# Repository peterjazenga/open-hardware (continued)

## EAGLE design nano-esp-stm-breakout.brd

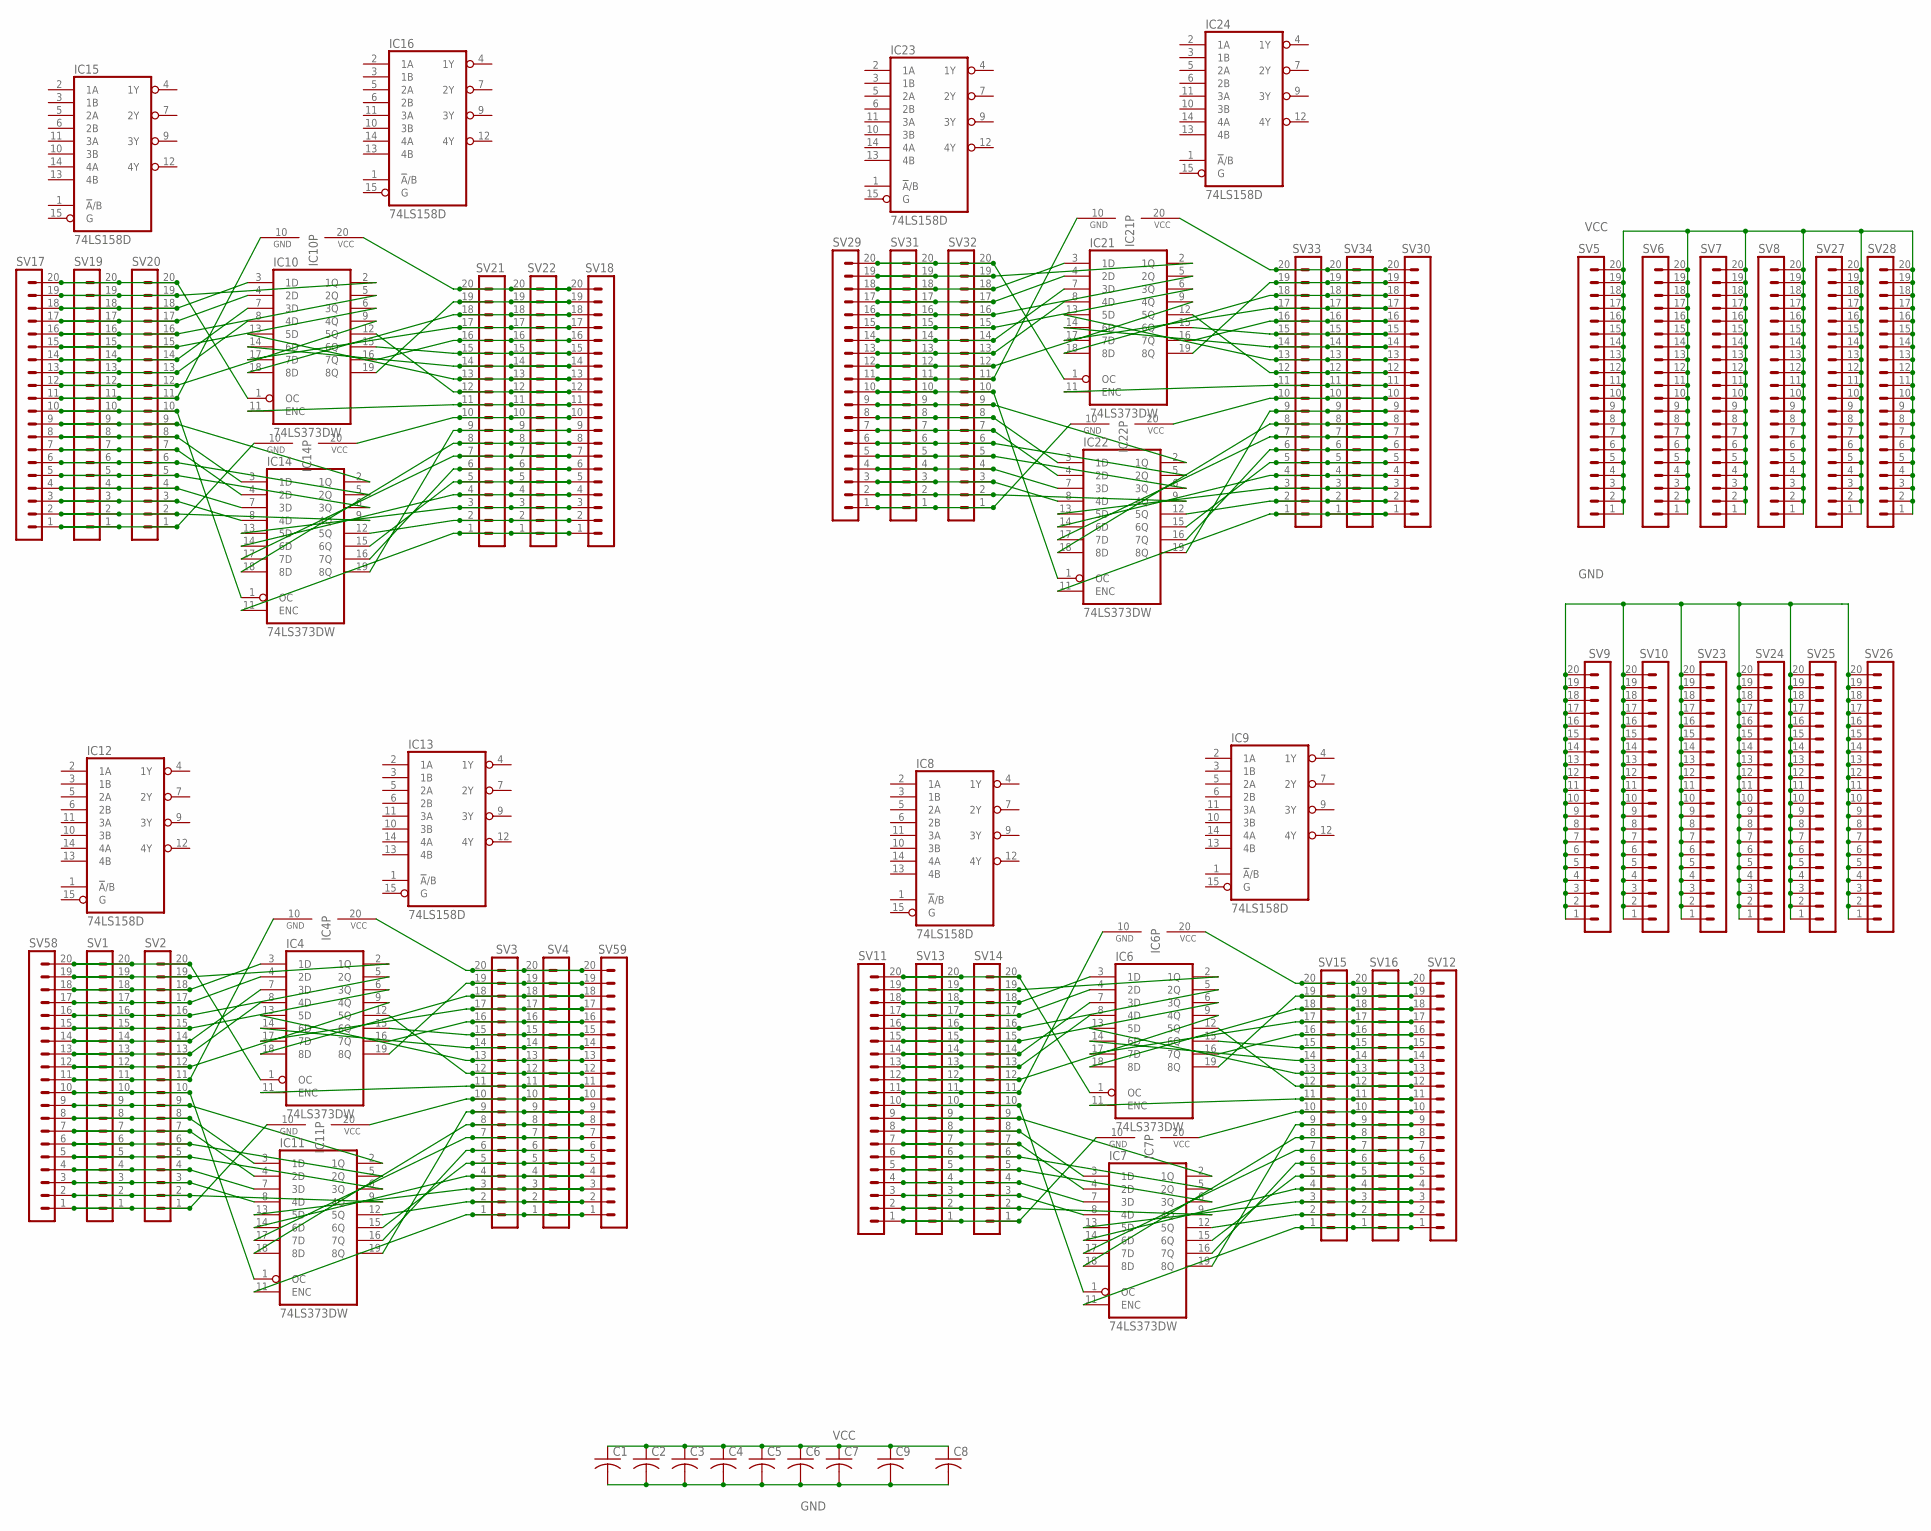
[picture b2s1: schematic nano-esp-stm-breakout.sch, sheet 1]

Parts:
C1, C2, C3, C4, C5, C6, C7, C8, C9: C-USC0805; C0805
IC4, IC6, IC7, IC10, IC11, IC14, IC21, IC22: 74LS373DW; SO20W
IC8, IC9, IC12, IC13, IC15, IC16, IC23, IC24: 74LS158D; SO16
SV1, SV2, SV3, SV4, SV5, SV6, SV7, SV8, SV9, SV10, SV11, SV12, SV13, SV14, SV15, SV16, SV17, SV18, SV19, SV20, SV21, SV22, SV23, SV24, SV25, SV26, SV27, SV28, SV29, SV30, SV31, SV32, SV33, SV34, SV58, SV59: MA20-1

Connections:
GND: C1.2, C2.2, C3.2, C4.2, C5.2, C6.2, C7.2, C8.2, C9.2, IC8.8 (GND), IC9.8 (GND), IC12.8 (GND), IC13.8 (GND), IC15.8 (GND), IC16.8 (GND), IC23.8 (GND), IC24.8 (GND), SV9.1, SV9.2, SV9.3, SV9.4, SV9.5, SV9.6, SV9.7, SV9.8, SV9.9, SV9.10, SV9.11, SV9.12, SV9.13, SV9.14, SV9.15, SV9.16, SV9.17, SV9.18, SV9.19, SV9.20, SV10.1, SV10.2, SV10.3, SV10.4, SV10.5, SV10.6, SV10.7, SV10.8, SV10.9, SV10.10, SV10.11, SV10.12, SV10.13, SV10.14, SV10.15, SV10.16, SV10.17, SV10.18, SV10.19, SV10.20, SV23.1, SV23.2, SV23.3, SV23.4, SV23.5, SV23.6, SV23.7, SV23.8, SV23.9, SV23.10, SV23.11, SV23.12, SV23.13, SV23.14, SV23.15, SV23.16, SV23.17, SV23.18, SV23.19, SV23.20, SV24.1, SV24.2, SV24.3, SV24.4, SV24.5, SV24.6, SV24.7, SV24.8, SV24.9, SV24.10, SV24.11, SV24.12, SV24.13, SV24.14, SV24.15, SV24.16, SV24.17, SV24.18, SV24.19, SV24.20, SV25.1, SV25.2, SV25.3, SV25.4, SV25.5, SV25.6, SV25.7, SV25.8, SV25.9, SV25.10, SV25.11, SV25.12, SV25.13, SV25.14, SV25.15, SV25.16, SV25.17, SV25.18, SV25.19, SV25.20, SV26.1, SV26.2, SV26.3, SV26.4, SV26.5, SV26.6, SV26.7, SV26.8, SV26.9, SV26.10, SV26.11, SV26.12, SV26.13, SV26.14, SV26.15, SV26.16, SV26.17, SV26.18, SV26.19, SV26.20; also elsewhere on the board
unnamed: IC7.9 (4Q), SV11.2, SV13.2, SV14.2
unnamed: IC7.7 (3D), SV11.4, SV13.4, SV14.4
unnamed: IC7.6 (3Q), SV11.5, SV13.5, SV14.5
unnamed: IC7.5 (2Q), SV11.6, SV13.6, SV14.6
unnamed: IC7.3 (1D), SV11.8, SV13.8, SV14.8
unnamed: IC7.2 (1Q), SV11.9, SV13.9, SV14.9
unnamed: IC7.1 (OC), SV11.10, SV13.10, SV14.10
unnamed: IC6.10 (GND), SV11.11, SV13.11, SV14.11
unnamed: IC6.9 (4Q), SV11.12, SV13.12, SV14.12
unnamed: IC6.7 (3D), SV11.14, SV13.14, SV14.14
unnamed: IC6.6 (3Q), SV11.15, SV13.15, SV14.15
unnamed: IC6.5 (2Q), SV11.16, SV13.16, SV14.16
unnamed: IC6.3 (1D), SV11.18, SV13.18, SV14.18
unnamed: IC6.2 (1Q), SV11.19, SV13.19, SV14.19
unnamed: IC6.1 (OC), SV11.20, SV13.20, SV14.20
unnamed: IC7.11 (ENC), SV12.1, SV15.1, SV16.1
unnamed: IC7.12 (5Q), SV12.2, SV15.2, SV16.2
unnamed: IC7.13 (5D), SV12.3, SV15.3, SV16.3
unnamed: IC7.14 (6D), SV12.4, SV15.4, SV16.4
unnamed: IC7.15 (6Q), SV12.5, SV15.5, SV16.5
unnamed: IC7.16 (7Q), SV12.6, SV15.6, SV16.6
unnamed: IC7.17 (7D), SV12.7, SV15.7, SV16.7
unnamed: IC7.18 (8D), SV12.8, SV15.8, SV16.8
unnamed: IC7.19 (8Q), SV12.9, SV15.9, SV16.9
unnamed: IC7.20 (VCC), SV12.10, SV15.10, SV16.10
unnamed: IC6.11 (ENC), SV12.11, SV15.11, SV16.11
unnamed: IC6.12 (5Q), SV12.12, SV15.12, SV16.12
unnamed: IC6.13 (5D), SV12.13, SV15.13, SV16.13
unnamed: IC6.14 (6D), SV12.14, SV15.14, SV16.14
unnamed: IC6.15 (6Q), SV12.15, SV15.15, SV16.15
unnamed: IC6.16 (7Q), SV12.16, SV15.16, SV16.16
unnamed: IC6.17 (7D), SV12.17, SV15.17, SV16.17
unnamed: IC6.18 (8D), SV12.18, SV15.18, SV16.18
unnamed: IC6.19 (8Q), SV12.19, SV15.19, SV16.19
unnamed: IC7.10 (GND), SV11.1, SV13.1, SV14.1
unnamed: IC7.8 (4D), SV11.3, SV13.3, SV14.3
unnamed: IC7.4 (2D), SV11.7, SV13.7, SV14.7
unnamed: IC6.8 (4D), SV11.13, SV13.13, SV14.13
unnamed: IC6.4 (2D), SV11.17, SV13.17, SV14.17
unnamed: IC6.20 (VCC), SV12.20, SV15.20, SV16.20
unnamed: IC14.9 (4Q), SV17.2, SV19.2, SV20.2
unnamed: IC14.7 (3D), SV17.4, SV19.4, SV20.4
unnamed: IC14.6 (3Q), SV17.5, SV19.5, SV20.5
unnamed: IC14.5 (2Q), SV17.6, SV19.6, SV20.6
unnamed: IC14.3 (1D), SV17.8, SV19.8, SV20.8
unnamed: IC14.2 (1Q), SV17.9, SV19.9, SV20.9
unnamed: IC14.1 (OC), SV17.10, SV19.10, SV20.10
unnamed: IC10.10 (GND), SV17.11, SV19.11, SV20.11
unnamed: IC10.9 (4Q), SV17.12, SV19.12, SV20.12
unnamed: IC10.7 (3D), SV17.14, SV19.14, SV20.14
unnamed: IC10.6 (3Q), SV17.15, SV19.15, SV20.15
unnamed: IC10.5 (2Q), SV17.16, SV19.16, SV20.16
unnamed: IC10.3 (1D), SV17.18, SV19.18, SV20.18
unnamed: IC10.2 (1Q), SV17.19, SV19.19, SV20.19
unnamed: IC10.1 (OC), SV17.20, SV19.20, SV20.20
unnamed: IC14.11 (ENC), SV18.1, SV21.1, SV22.1
unnamed: IC14.12 (5Q), SV18.2, SV21.2, SV22.2
unnamed: IC14.13 (5D), SV18.3, SV21.3, SV22.3
unnamed: IC14.14 (6D), SV18.4, SV21.4, SV22.4
unnamed: IC14.15 (6Q), SV18.5, SV21.5, SV22.5
unnamed: IC14.16 (7Q), SV18.6, SV21.6, SV22.6
unnamed: IC14.17 (7D), SV18.7, SV21.7, SV22.7
unnamed: IC14.18 (8D), SV18.8, SV21.8, SV22.8
unnamed: IC14.19 (8Q), SV18.9, SV21.9, SV22.9
unnamed: IC14.20 (VCC), SV18.10, SV21.10, SV22.10
unnamed: IC10.11 (ENC), SV18.11, SV21.11, SV22.11
unnamed: IC10.12 (5Q), SV18.12, SV21.12, SV22.12
unnamed: IC10.13 (5D), SV18.13, SV21.13, SV22.13
unnamed: IC10.14 (6D), SV18.14, SV21.14, SV22.14
unnamed: IC10.15 (6Q), SV18.15, SV21.15, SV22.15
unnamed: IC10.16 (7Q), SV18.16, SV21.16, SV22.16
unnamed: IC10.17 (7D), SV18.17, SV21.17, SV22.17
unnamed: IC10.18 (8D), SV18.18, SV21.18, SV22.18
unnamed: IC10.19 (8Q), SV18.19, SV21.19, SV22.19
unnamed: IC14.10 (GND), SV17.1, SV19.1, SV20.1
unnamed: IC14.8 (4D), SV17.3, SV19.3, SV20.3
unnamed: IC14.4 (2D), SV17.7, SV19.7, SV20.7
unnamed: IC10.8 (4D), SV17.13, SV19.13, SV20.13
unnamed: IC10.4 (2D), SV17.17, SV19.17, SV20.17
unnamed: IC10.20 (VCC), SV18.20, SV21.20, SV22.20
unnamed: IC22.9 (4Q), SV29.2, SV31.2, SV32.2
unnamed: IC22.7 (3D), SV29.4, SV31.4, SV32.4
unnamed: IC22.6 (3Q), SV29.5, SV31.5, SV32.5
unnamed: IC22.5 (2Q), SV29.6, SV31.6, SV32.6
unnamed: IC22.3 (1D), SV29.8, SV31.8, SV32.8
unnamed: IC22.2 (1Q), SV29.9, SV31.9, SV32.9
unnamed: IC22.1 (OC), SV29.10, SV31.10, SV32.10
unnamed: IC21.10 (GND), SV29.11, SV31.11, SV32.11
unnamed: IC21.9 (4Q), SV29.12, SV31.12, SV32.12
unnamed: IC21.7 (3D), SV29.14, SV31.14, SV32.14
unnamed: IC21.6 (3Q), SV29.15, SV31.15, SV32.15
unnamed: IC21.5 (2Q), SV29.16, SV31.16, SV32.16
unnamed: IC21.3 (1D), SV29.18, SV31.18, SV32.18
unnamed: IC21.2 (1Q), SV29.19, SV31.19, SV32.19
unnamed: IC21.1 (OC), SV29.20, SV31.20, SV32.20
unnamed: IC22.11 (ENC), SV30.1, SV33.1, SV34.1
unnamed: IC22.12 (5Q), SV30.2, SV33.2, SV34.2
unnamed: IC22.13 (5D), SV30.3, SV33.3, SV34.3
unnamed: IC22.14 (6D), SV30.4, SV33.4, SV34.4
unnamed: IC22.15 (6Q), SV30.5, SV33.5, SV34.5
unnamed: IC22.16 (7Q), SV30.6, SV33.6, SV34.6
unnamed: IC22.17 (7D), SV30.7, SV33.7, SV34.7
unnamed: IC22.18 (8D), SV30.8, SV33.8, SV34.8
unnamed: IC22.19 (8Q), SV30.9, SV33.9, SV34.9
unnamed: IC22.20 (VCC), SV30.10, SV33.10, SV34.10
unnamed: IC21.11 (ENC), SV30.11, SV33.11, SV34.11
unnamed: IC21.12 (5Q), SV30.12, SV33.12, SV34.12
unnamed: IC21.13 (5D), SV30.13, SV33.13, SV34.13
unnamed: IC21.14 (6D), SV30.14, SV33.14, SV34.14
unnamed: IC21.15 (6Q), SV30.15, SV33.15, SV34.15
unnamed: IC21.16 (7Q), SV30.16, SV33.16, SV34.16
unnamed: IC21.17 (7D), SV30.17, SV33.17, SV34.17
unnamed: IC21.18 (8D), SV30.18, SV33.18, SV34.18
unnamed: IC21.19 (8Q), SV30.19, SV33.19, SV34.19
unnamed: IC22.10 (GND), SV29.1, SV31.1, SV32.1
unnamed: IC22.8 (4D), SV29.3, SV31.3, SV32.3
unnamed: IC22.4 (2D), SV29.7, SV31.7, SV32.7
unnamed: IC21.8 (4D), SV29.13, SV31.13, SV32.13
unnamed: IC21.4 (2D), SV29.17, SV31.17, SV32.17
unnamed: IC21.20 (VCC), SV30.20, SV33.20, SV34.20
unnamed: IC11.9 (4Q), SV1.2, SV2.2, SV58.2
unnamed: IC11.7 (3D), SV1.4, SV2.4, SV58.4
unnamed: IC11.6 (3Q), SV1.5, SV2.5, SV58.5
unnamed: IC11.5 (2Q), SV1.6, SV2.6, SV58.6
unnamed: IC11.3 (1D), SV1.8, SV2.8, SV58.8
unnamed: IC11.2 (1Q), SV1.9, SV2.9, SV58.9
unnamed: IC11.1 (OC), SV1.10, SV2.10, SV58.10
unnamed: IC4.10 (GND), SV1.11, SV2.11, SV58.11
unnamed: IC4.9 (4Q), SV1.12, SV2.12, SV58.12
unnamed: IC4.7 (3D), SV1.14, SV2.14, SV58.14
unnamed: IC4.6 (3Q), SV1.15, SV2.15, SV58.15
unnamed: IC4.5 (2Q), SV1.16, SV2.16, SV58.16
unnamed: IC4.3 (1D), SV1.18, SV2.18, SV58.18
unnamed: IC4.2 (1Q), SV1.19, SV2.19, SV58.19
unnamed: IC4.1 (OC), SV1.20, SV2.20, SV58.20
unnamed: IC11.11 (ENC), SV3.1, SV4.1, SV59.1
unnamed: IC11.12 (5Q), SV3.2, SV4.2, SV59.2
unnamed: IC11.13 (5D), SV3.3, SV4.3, SV59.3
unnamed: IC11.14 (6D), SV3.4, SV4.4, SV59.4
unnamed: IC11.15 (6Q), SV3.5, SV4.5, SV59.5
unnamed: IC11.16 (7Q), SV3.6, SV4.6, SV59.6
unnamed: IC11.17 (7D), SV3.7, SV4.7, SV59.7
unnamed: IC11.18 (8D), SV3.8, SV4.8, SV59.8
unnamed: IC11.19 (8Q), SV3.9, SV4.9, SV59.9
unnamed: IC11.20 (VCC), SV3.10, SV4.10, SV59.10
unnamed: IC4.11 (ENC), SV3.11, SV4.11, SV59.11
unnamed: IC4.12 (5Q), SV3.12, SV4.12, SV59.12
unnamed: IC4.13 (5D), SV3.13, SV4.13, SV59.13
unnamed: IC4.14 (6D), SV3.14, SV4.14, SV59.14
unnamed: IC4.15 (6Q), SV3.15, SV4.15, SV59.15
unnamed: IC4.16 (7Q), SV3.16, SV4.16, SV59.16
unnamed: IC4.17 (7D), SV3.17, SV4.17, SV59.17
unnamed: IC4.18 (8D), SV3.18, SV4.18, SV59.18
unnamed: IC4.19 (8Q), SV3.19, SV4.19, SV59.19
unnamed: IC11.10 (GND), SV1.1, SV2.1, SV58.1
unnamed: IC11.8 (4D), SV1.3, SV2.3, SV58.3
unnamed: IC11.4 (2D), SV1.7, SV2.7, SV58.7
unnamed: IC4.8 (4D), SV1.13, SV2.13, SV58.13
unnamed: IC4.4 (2D), SV1.17, SV2.17, SV58.17
unnamed: IC4.20 (VCC), SV3.20, SV4.20, SV59.20
VCC: C1.1, C2.1, C3.1, C4.1, C5.1, C6.1, C7.1, C8.1, C9.1, IC8.16 (VCC), IC9.16 (VCC), IC12.16 (VCC), IC13.16 (VCC), IC15.16 (VCC), IC16.16 (VCC), IC23.16 (VCC), IC24.16 (VCC), SV5.1, SV5.2, SV5.3, SV5.4, SV5.5, SV5.6, SV5.7, SV5.8, SV5.9, SV5.10, SV5.11, SV5.12, SV5.13, SV5.14, SV5.15, SV5.16, SV5.17, SV5.18, SV5.19, SV5.20, SV6.1, SV6.2, SV6.3, SV6.4, SV6.5, SV6.6, SV6.7, SV6.8, SV6.9, SV6.10, SV6.11, SV6.12, SV6.13, SV6.14, SV6.15, SV6.16, SV6.17, SV6.18, SV6.19, SV6.20, SV7.1, SV7.2, SV7.3, SV7.4, SV7.5, SV7.6, SV7.7, SV7.8, SV7.9, SV7.10, SV7.11, SV7.12, SV7.13, SV7.14, SV7.15, SV7.16, SV7.17, SV7.18, SV7.19, SV7.20, SV8.1, SV8.2, SV8.3, SV8.4, SV8.5, SV8.6, SV8.7, SV8.8, SV8.9, SV8.10, SV8.11, SV8.12, SV8.13, SV8.14, SV8.15, SV8.16, SV8.17, SV8.18, SV8.19, SV8.20, SV27.1, SV27.2, SV27.3, SV27.4, SV27.5, SV27.6, SV27.7, SV27.8, SV27.9, SV27.10, SV27.11, SV27.12, SV27.13, SV27.14, SV27.15, SV27.16, SV27.17, SV27.18, SV27.19, SV27.20, SV28.1, SV28.2, SV28.3, SV28.4, SV28.5, SV28.6, SV28.7, SV28.8, SV28.9, SV28.10, SV28.11, SV28.12, SV28.13, SV28.14, SV28.15, SV28.16, SV28.17, SV28.18, SV28.19, SV28.20; also elsewhere on the board

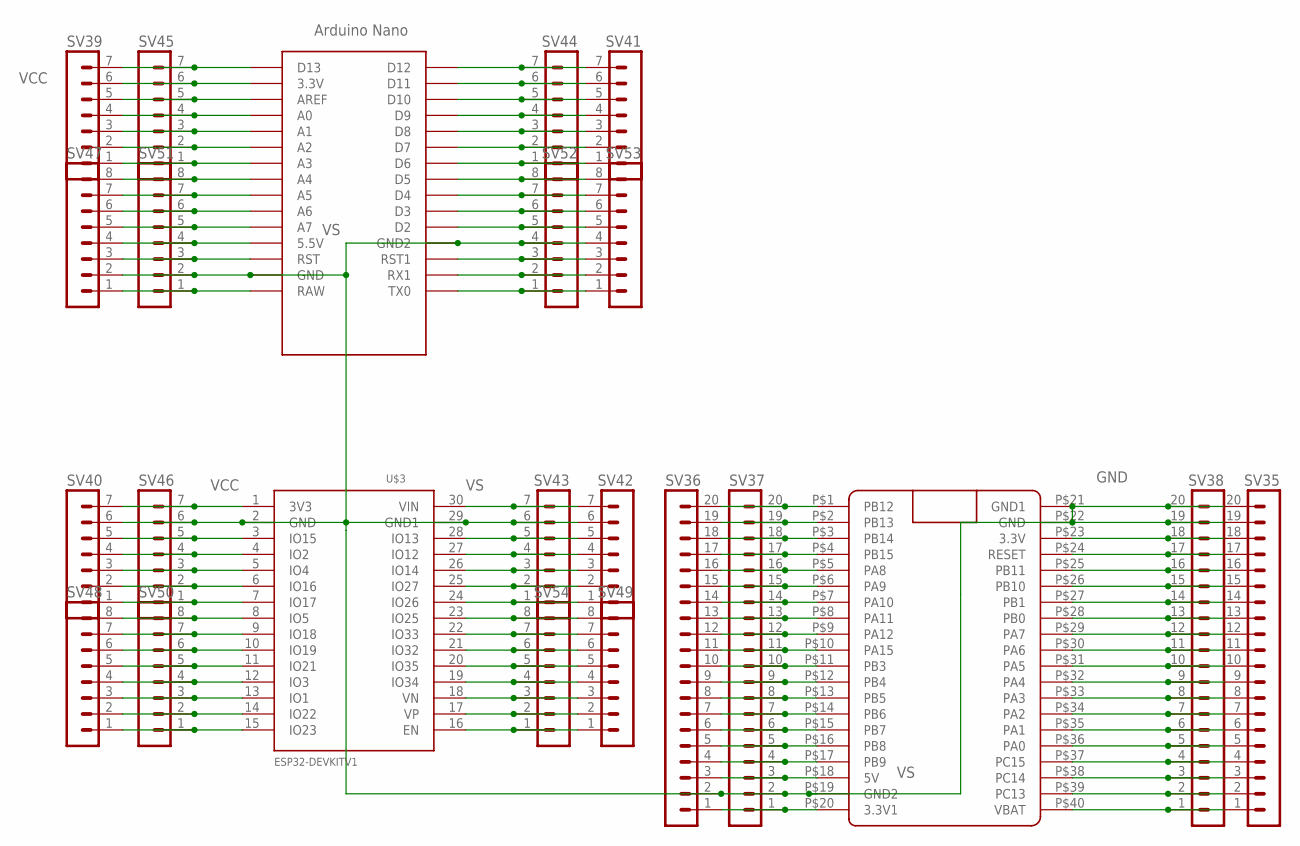
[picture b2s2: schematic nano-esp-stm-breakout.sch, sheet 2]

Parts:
SV35, SV36, SV37, SV38: MA20-1
SV39, SV40, SV41, SV42, SV43, SV44, SV45, SV46: MA07-1
SV47, SV48, SV49, SV50, SV51, SV52, SV53, SV54: MA08-1
U$1: NANO
U$2: BLUE_PILL
U$3: ESP32DEVKITV1; ESP32-DEVKITV1

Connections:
GND: SV35.19, SV35.20, SV36.2, SV37.2, SV38.19, SV38.20, SV40.6, SV42.6, SV43.6, SV46.6, SV47.2, SV51.2, SV52.4, SV53.4, U$1.GND, U$1.GND1 (GND2), U$2.P$19 (GND2), U$2.P$21 (GND1), U$2.P$22 (GND), U$3.2 (GND), U$3.29 (GND1); also elsewhere on the board
unnamed: SV39.1, SV45.1, U$1.A3
unnamed: SV39.2, SV45.2, U$1.A2
unnamed: SV35.18, SV38.18, U$2.P$23 (3.3V)
unnamed: SV35.17, SV38.17, U$2.P$24 (RESET)
unnamed: SV35.16, SV38.16, U$2.P$25 (PB11)
unnamed: SV35.15, SV38.15, U$2.P$26 (PB10)
unnamed: SV35.14, SV38.14, U$2.P$27 (PB1)
unnamed: SV35.13, SV38.13, U$2.P$28 (PB0)
unnamed: SV35.12, SV38.12, U$2.P$29 (PA7)
unnamed: SV35.11, SV38.11, U$2.P$30 (PA6)
unnamed: SV35.10, SV38.10, U$2.P$31 (PA5)
unnamed: SV35.9, SV38.9, U$2.P$32 (PA4)
unnamed: SV35.8, SV38.8, U$2.P$33 (PA3)
unnamed: SV35.7, SV38.7, U$2.P$34 (PA2)
unnamed: SV35.6, SV38.6, U$2.P$35 (PA1)
unnamed: SV35.5, SV38.5, U$2.P$36 (PA0)
unnamed: SV35.4, SV38.4, U$2.P$37 (PC15)
unnamed: SV35.3, SV38.3, U$2.P$38 (PC14)
unnamed: SV35.2, SV38.2, U$2.P$39 (PC13)
unnamed: SV35.1, SV38.1, U$2.P$40 (VBAT)
unnamed: SV36.1, SV37.1, U$2.P$20 (3.3V1)
unnamed: SV39.3, SV45.3, U$1.A1
unnamed: SV36.4, SV37.4, U$2.P$17 (PB9)
unnamed: SV36.5, SV37.5, U$2.P$16 (PB8)
unnamed: SV36.6, SV37.6, U$2.P$15 (PB7)
unnamed: SV36.7, SV37.7, U$2.P$14 (PB6)
unnamed: SV36.8, SV37.8, U$2.P$13 (PB5)
unnamed: SV36.9, SV37.9, U$2.P$12 (PB4)
unnamed: SV36.10, SV37.10, U$2.P$11 (PB3)
unnamed: SV36.11, SV37.11, U$2.P$10 (PA15)
unnamed: SV36.12, SV37.12, U$2.P$9 (PA12)
unnamed: SV36.13, SV37.13, U$2.P$8 (PA11)
unnamed: SV36.14, SV37.14, U$2.P$7 (PA10)
unnamed: SV36.15, SV37.15, U$2.P$6 (PA9)
unnamed: SV36.16, SV37.16, U$2.P$5 (PA8)
unnamed: SV36.17, SV37.17, U$2.P$4 (PB15)
unnamed: SV36.18, SV37.18, U$2.P$3 (PB14)
unnamed: SV36.19, SV37.19, U$2.P$2 (PB13)
unnamed: SV36.20, SV37.20, U$2.P$1 (PB12)
unnamed: SV39.4, SV45.4, U$1.A0
unnamed: SV39.5, SV45.5, U$1.AREF
unnamed: SV39.7, SV45.7, U$1.D13
unnamed: SV40.1, SV46.1, U$3.7 (IO17)
unnamed: SV40.2, SV46.2, U$3.6 (IO16)
unnamed: SV40.3, SV46.3, U$3.5 (IO4)
unnamed: SV40.4, SV46.4, U$3.4 (IO2)
unnamed: SV40.5, SV46.5, U$3.3 (IO15)
unnamed: SV41.1, SV44.1, U$1.D6
unnamed: SV41.2, SV44.2, U$1.D7
unnamed: SV41.3, SV44.3, U$1.D8
unnamed: SV41.4, SV44.4, U$1.D9
unnamed: SV41.5, SV44.5, U$1.D10
unnamed: SV41.6, SV44.6, U$1.D11
unnamed: SV41.7, SV44.7, U$1.D12
unnamed: SV42.1, SV43.1, U$3.24 (IO26)
unnamed: SV42.2, SV43.2, U$3.25 (IO27)
unnamed: SV42.3, SV43.3, U$3.26 (IO14)
unnamed: SV42.4, SV43.4, U$3.27 (IO12)
unnamed: SV42.5, SV43.5, U$3.28 (IO13)
unnamed: SV47.1, SV51.1, U$1.RAW
unnamed: SV47.3, SV51.3, U$1.RST
unnamed: SV47.5, SV51.5, U$1.A7
unnamed: SV47.6, SV51.6, U$1.A6
unnamed: SV47.7, SV51.7, U$1.A5
unnamed: SV47.8, SV51.8, U$1.A4
unnamed: SV49.1, SV54.1, U$3.16 (EN)
unnamed: SV49.2, SV54.2, U$3.17 (VP)
unnamed: SV49.3, SV54.3, U$3.18 (VN)
unnamed: SV49.4, SV54.4, U$3.19 (IO34)
unnamed: SV49.5, SV54.5, U$3.20 (IO35)
unnamed: SV49.6, SV54.6, U$3.21 (IO32)
unnamed: SV49.7, SV54.7, U$3.22 (IO33)
unnamed: SV49.8, SV54.8, U$3.23 (IO25)
unnamed: SV52.1, SV53.1, U$1.TX0
unnamed: SV52.2, SV53.2, U$1.RX1
unnamed: SV52.3, SV53.3, U$1.RST1
unnamed: SV52.5, SV53.5, U$1.D2
unnamed: SV52.6, SV53.6, U$1.D3
unnamed: SV52.7, SV53.7, U$1.D4
unnamed: SV52.8, SV53.8, U$1.D5
unnamed: SV48.1, SV50.1, U$3.15 (IO23)
unnamed: SV48.2, SV50.2, U$3.14 (IO22)
unnamed: SV48.3, SV50.3, U$3.13 (IO1)
unnamed: SV48.4, SV50.4, U$3.12 (IO3)
unnamed: SV48.5, SV50.5, U$3.11 (IO21)
unnamed: SV48.6, SV50.6, U$3.10 (IO19)
unnamed: SV48.7, SV50.7, U$3.9 (IO18)
unnamed: SV48.8, SV50.8, U$3.8 (IO5)
VCC: SV39.6, SV40.7, SV45.6, SV46.7, U$1.3.3V, U$3.1 (3V3); also elsewhere on the board
VS: SV36.3, SV37.3, SV42.7, SV43.7, SV47.4, SV51.4, U$1.5V (5.5V), U$2.P$18 (5V), U$3.30 (VIN)

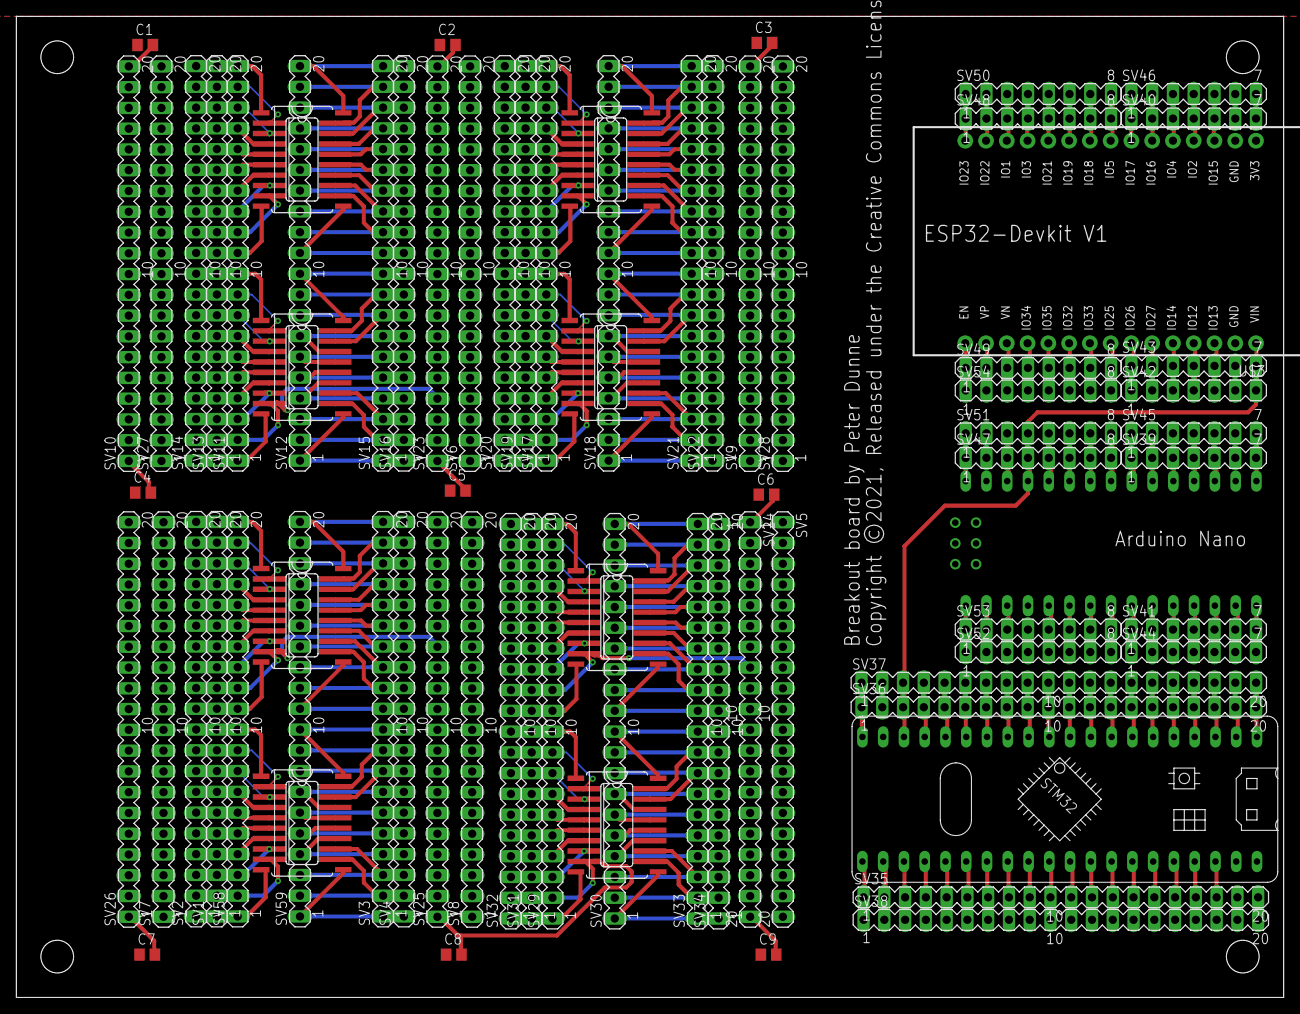
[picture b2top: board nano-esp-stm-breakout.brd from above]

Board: 2 copper layers, 155.0 x 120.0 mm, 84 parts (0 on the bottom side), 251 nets.

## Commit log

2021-02-28 breakout boards
    these breakout boards are designed to make it easier to create simple projects by combining basic breadboard features with sockets for ESP32, Arduino Nano and Bluepill on the same PCB
    It can take up to 8 SMD IC's or a combination of DIL IC's or a mix of both due to the unique layout
2021-02-28 added STM32 breadboard
    added STM32 breakout board
